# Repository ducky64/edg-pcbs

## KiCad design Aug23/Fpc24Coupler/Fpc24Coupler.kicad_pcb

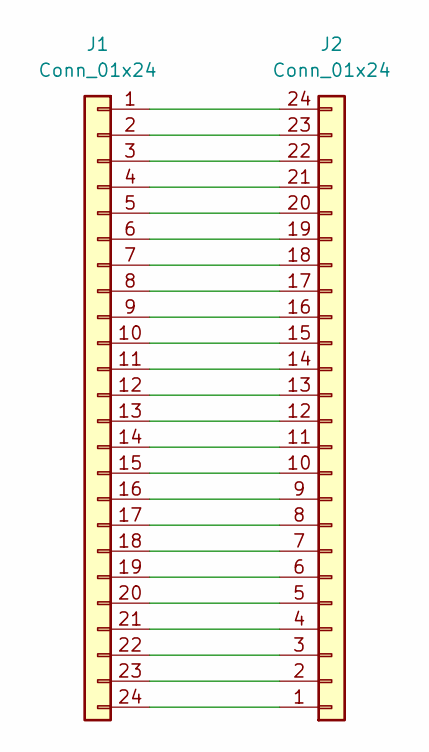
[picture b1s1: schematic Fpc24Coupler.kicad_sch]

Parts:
J1, J2: Conn_01x24; Hirose_FH12-24S-0.5SH_1x24-1MP_P0.50mm_Horizontal

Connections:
unnamed: J1.1, J2.24
unnamed: J1.2, J2.23
unnamed: J1.3, J2.22
unnamed: J1.4, J2.21
unnamed: J1.5, J2.20
unnamed: J1.6, J2.19
unnamed: J1.7, J2.18
unnamed: J1.8, J2.17
unnamed: J1.9, J2.16
unnamed: J1.10, J2.15
unnamed: J1.11, J2.14
unnamed: J1.12, J2.13
unnamed: J1.13, J2.12
unnamed: J1.14, J2.11
unnamed: J1.15, J2.10
unnamed: J1.16, J2.9
unnamed: J1.17, J2.8
unnamed: J1.18, J2.7
unnamed: J1.19, J2.6
unnamed: J1.20, J2.5
unnamed: J1.21, J2.4
unnamed: J1.22, J2.3
unnamed: J1.23, J2.2
unnamed: J1.24, J2.1

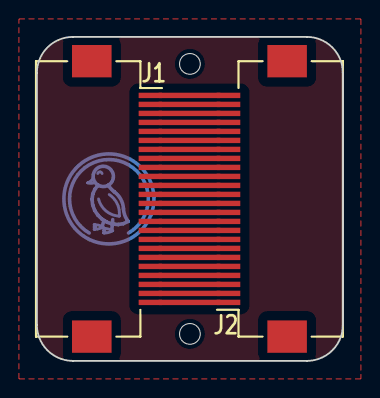
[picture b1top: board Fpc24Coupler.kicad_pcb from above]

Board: 2 copper layers, 17.0 x 18.0 mm, 4 parts (2 on the bottom side), 24 nets.

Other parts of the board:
UU4: Duck; Symbol_Duckling
UU5: Lemur; Symbol_LemurSmall

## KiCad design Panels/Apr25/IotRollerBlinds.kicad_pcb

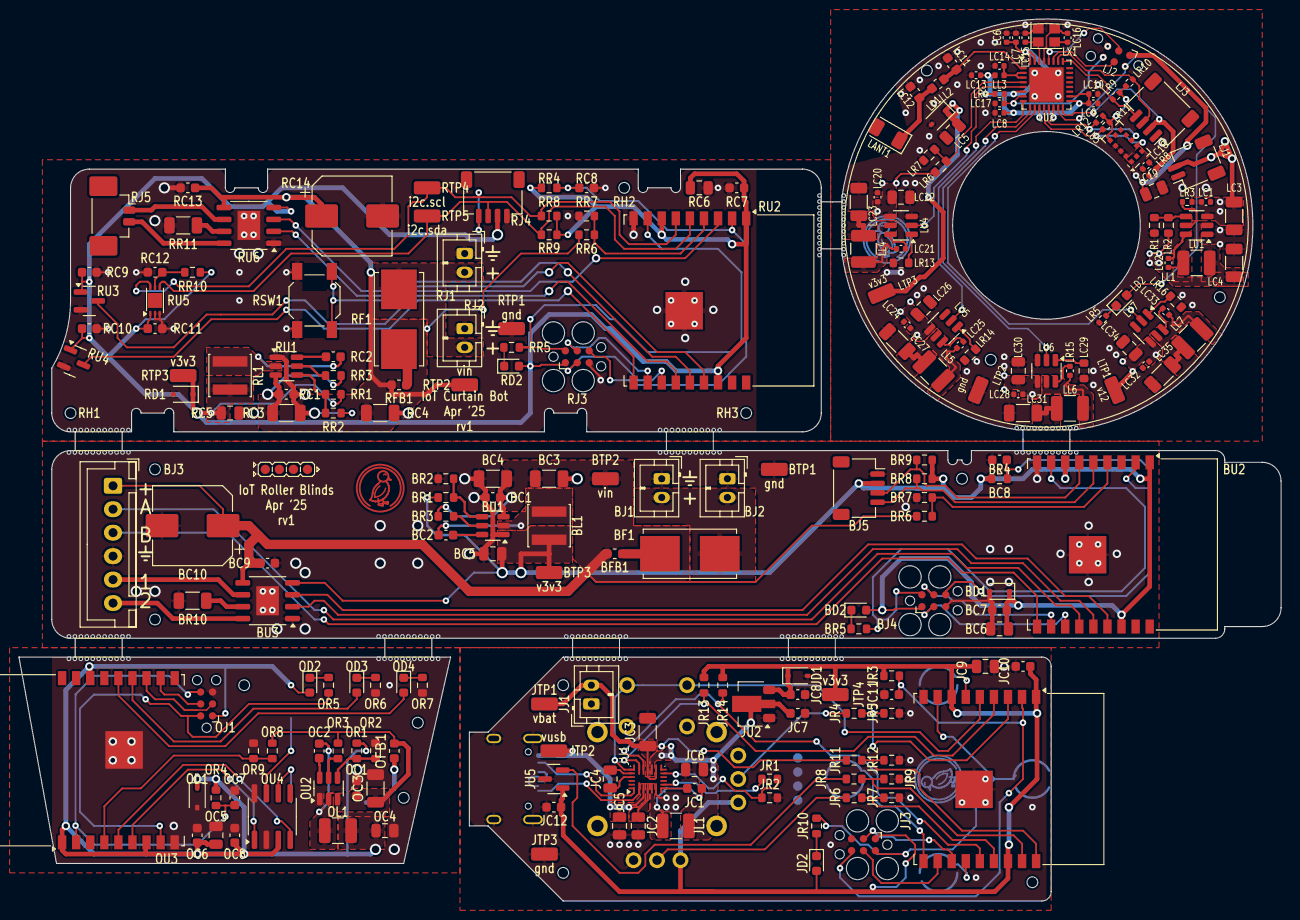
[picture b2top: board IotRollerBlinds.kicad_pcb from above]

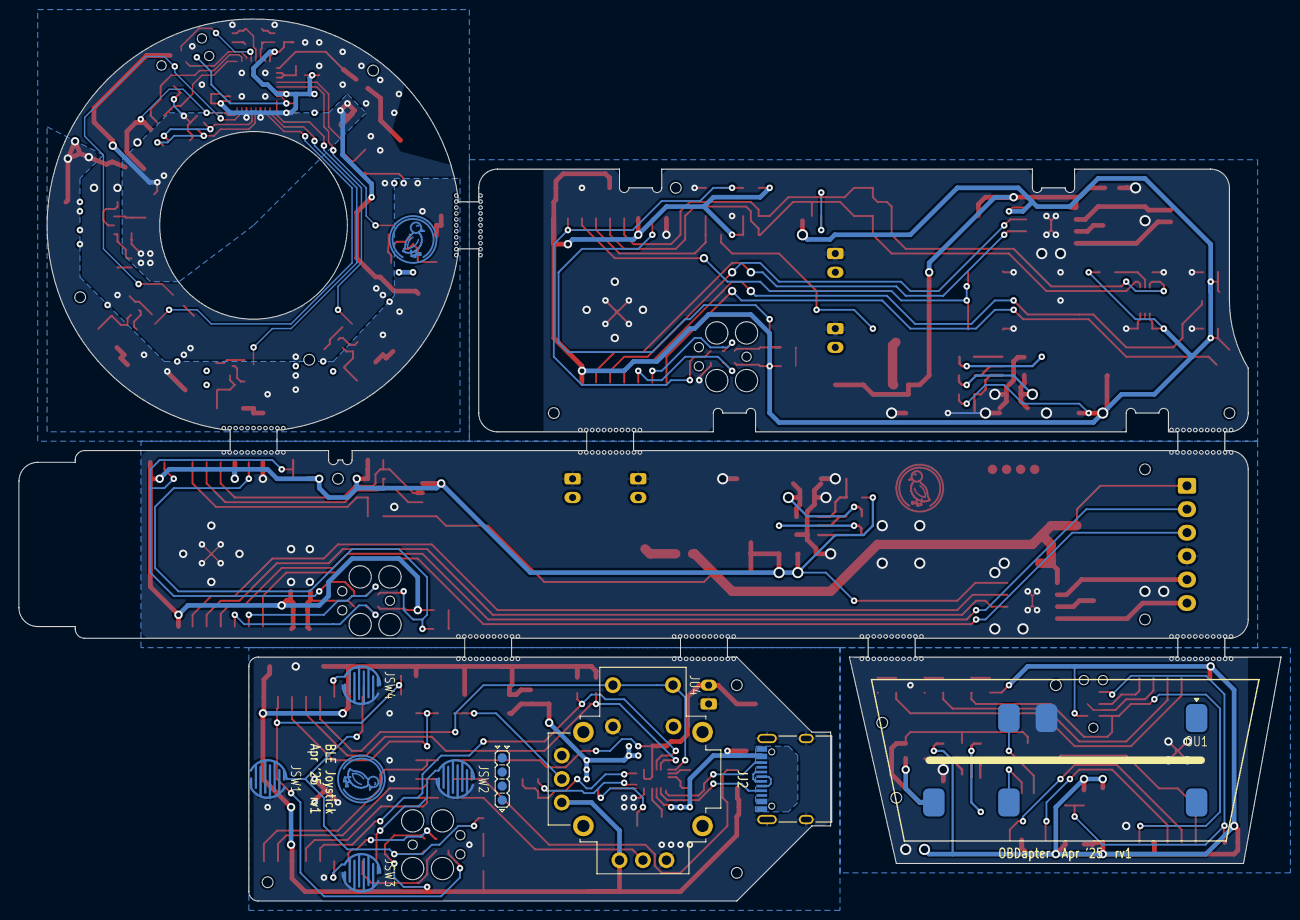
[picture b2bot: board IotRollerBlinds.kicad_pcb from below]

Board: 2 copper layers, 134.5 x 94.0 mm, 249 parts (9 on the bottom side), 148 nets.

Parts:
BC1: reg_3v3.hf_in_cap; C_0603_1608Metric
BC2: reg_3v3.boot_cap; C_0603_1608Metric
BC3: reg_3v3.power_path.in_cap.c[0]; C_1206_3216Metric
BC4: reg_3v3.power_path.in_cap.c[1]; C_1206_3216Metric
BC5: reg_3v3.power_path.out_cap; C_0805_2012Metric
BC6: mcu.vcc_cap0; C_0805_2012Metric
BC7: mcu.vcc_cap1; C_0603_1608Metric
BC8: mcu.en_pull.c; C_0603_1608Metric
BC9: drv.vm_cap0; C_0603_1608Metric
BC10: drv.vm_cap1; CP_Elec_8x10
BD1: prot_3v3; D_SOD-323
BD2: ledr.package; LED_0603_1608Metric
BF1: fuse; Fuseholder_Littelfuse_Nano2_154x
BFB1: ferrite; L_0603_1608Metric
BH1: jlc_th.th1; JlcToolingHole_1.152mm
BH2: jlc_th.th2; JlcToolingHole_1.152mm
BH3: jlc_th.th3; JlcToolingHole_1.152mm
BJ1: pwr; JST_PH_B2B-PH-K_1x02_P2.00mm_Vertical
BJ2: pwr_out; JST_PH_B2B-PH-K_1x02_P2.00mm_Vertical
BJ3: conn; JST_XH_B6B-XH-A_1x06_P2.50mm_Vertical
BJ4: mcu.prog; Tag-Connect_TC2030-IDC-FP_2x03_P1.27mm_Vertical
BJ5: qwiic; JST_SH_SM04B-SRSS-TB_1x04-1MP_P1.00mm_Horizontal
BL1: reg_3v3.power_path.inductor; L_Sunlord_SWPA4030S
BR1: reg_3v3.fb.top_res; R_0603_1608Metric
BR2: reg_3v3.fb.bottom_res; R_0603_1608Metric
BR3: reg_3v3.en_res; R_0603_1608Metric
BR4: mcu.en_pull.r; R_0603_1608Metric
BR5: ledr.res; R_0603_1608Metric
BR6: vin_sense.top_res; R_0603_1608Metric
BR7: vin_sense.bottom_res; R_0603_1608Metric
BR8: qwiic_pull.scl_res; R_0603_1608Metric
BR9: qwiic_pull.sda_res; R_0603_1608Metric
BR10: drv.isen_res; R_1206_3216Metric
BTP1: gnd; TestPoint_TE_RCT_0805
BTP2: vin; TestPoint_TE_RCT_0805
BTP3: v3v3; TestPoint_TE_RCT_0805
BU1: reg_3v3.ic; SOT-23-6
BU2: mcu.ic; ESP-WROOM-02
BU3: drv.ic; HSOP-8-1EP_3.9x4.9mm_P1.27mm_EP2.41x3.1mm
JC1: mp2722.vbst_cap; C_0603_1608Metric
JC2: mp2722.pmid_cap; C_0805_2012Metric
JC3: mp2722.batt_cap; C_1206_3216Metric
JC4: mp2722.vcc_cap; C_0805_2012Metric
JC5: mp2722.power_path.in_cap; C_0805_2012Metric
JC6: mp2722.power_path.out_cap; C_0805_2012Metric
JC7: reg_3v3.in_cap; C_0603_1608Metric
JC8: reg_3v3.out_cap; C_0603_1608Metric
JC9: mcu.vcc_cap0; C_0805_2012Metric
JC10: mcu.vcc_cap1; C_0603_1608Metric
JC11: mcu.en_pull.c; C_0603_1608Metric
JC12: trig.cbyp; C_0603_1608Metric
JD1: prot_3v3; D_SOD-323
JD2: ledr.package; LED_0603_1608Metric
JH1: jlc_th.th1; JlcToolingHole_1.152mm
JH2: jlc_th.th2; JlcToolingHole_1.152mm
JH3: jlc_th.th3; JlcToolingHole_1.152mm
JJ1: bat; JST_PH_B2B-PH-K_1x02_P2.00mm_Vertical
JJ2: usb; USB_C_Receptacle_XKB_U262-16XN-4BVC11
JJ3: mcu.prog; Tag-Connect_TC2030-IDC-FP_2x03_P1.27mm_Vertical
JL1: mp2722.power_path.inductor; L_1210_3225Metric
JR1: fake_ntc.top_res; R_0603_1608Metric
JR2: fake_ntc.bottom_res; R_0603_1608Metric
JR3: mcu.en_pull.r; R_0603_1608Metric
JR4: ax1_div.top_res; R_0603_1608Metric
JR5: ax1_div.bottom_res; R_0603_1608Metric
JR6: ax2_div.top_res; R_0603_1608Metric
JR7: ax2_div.bottom_res; R_0603_1608Metric
JR8: trig_div.top_res; R_0603_1608Metric
JR9: trig_div.bottom_res; R_0603_1608Metric
JR10: ledr.res; R_0603_1608Metric
JR11: vbat_sense.top_res; R_0603_1608Metric
JR12: vbat_sense.bottom_res; R_0603_1608Metric
JR13: i2c_pull.scl_res; R_0603_1608Metric
JR14: i2c_pull.sda_res; R_0603_1608Metric
JSW1: mcu.boot; MembraneSwitch_4mm
JSW2: sw[0]; MembraneSwitch_4mm
JSW3: sw[1]; MembraneSwitch_4mm
JSW4: sw[2]; MembraneSwitch_4mm
JTP1: vbat; TestPoint_TE_RCT_0805
JTP2: vusb; TestPoint_TE_RCT_0805
JTP3: gnd; TestPoint_TE_RCT_0805
JTP4: v3v3; TestPoint_TE_RCT_0805
JU1: mp2722.ic; MPS_QFN-22_2.5x3.5mm_P0.4mm
JU2: reg_3v3.ic; SOT-89-3
JU3: mcu.ic; ESP-WROOM-02
JU4: stick; Joystick_XboxElite2
JU5: trig.ic; SOT-23
LANT1: mcu.ant; D_1206_3216Metric
LC1: reg_3v3.hf_in_cap; C_0402_1005Metric
LC2: reg_3v3.boot_cap; C_0402_1005Metric
LC3: reg_3v3.power_path.in_cap; C_1206_3216Metric
LC4: reg_3v3.power_path.out_cap; C_1206_3216Metric
LC5: mcu.vdd_bulk_cap; C_0805_2012Metric
LC6: mcu.vdda_cap0; C_0402_1005Metric
LC7: mcu.vdda_cap1; C_0402_1005Metric
LC8: mcu.vddrtc_cap; C_0402_1005Metric
LC9: mcu.vddcpu_cap; C_0402_1005Metric
LC10: mcu.vddspi_cap; C_0402_1005Metric
LC11: mcu.pi.c1; C_0603_1608Metric
LC12: mcu.pi.c2; C_0603_1608Metric
LC13: mcu.vdd3p3_l_cap; C_0402_1005Metric
LC14: mcu.vdd3p3_cap; C_0402_1005Metric
LC15: mcu.crystal.cap_a; C_0402_1005Metric
LC16: mcu.crystal.cap_b; C_0402_1005Metric
LC17: mcu.en_pull.c; C_0402_1005Metric
LC18: tof.vdd_cap[0]; C_0402_1005Metric
LC19: tof.vdd_cap[1]; C_0805_2012Metric
LC20: led_drv[0].cap; C_0402_1005Metric
LC21: led_drv[0].boot_cap; C_0402_1005Metric
LC22: led_drv[0].power_path.in_cap; C_0805_2012Metric
LC23: led_drv[0].power_path.out_cap; C_1206_3216Metric
LC24: led_drv[1].cap; C_0402_1005Metric
LC25: led_drv[1].boot_cap; C_0402_1005Metric
LC26: led_drv[1].power_path.in_cap; C_0805_2012Metric
LC27: led_drv[1].power_path.out_cap; C_1206_3216Metric
LC28: led_drv[2].cap; C_0402_1005Metric
LC29: led_drv[2].boot_cap; C_0402_1005Metric
LC30: led_drv[2].power_path.in_cap; C_0805_2012Metric
LC31: led_drv[2].power_path.out_cap; C_1206_3216Metric
LC32: led_drv[3].cap; C_0402_1005Metric
LC33: led_drv[3].boot_cap; C_0402_1005Metric
LC34: led_drv[3].power_path.in_cap; C_0805_2012Metric
LC35: led_drv[3].power_path.out_cap; C_1206_3216Metric
LD1: prot_3v3; D_SOD-323
LD2: ledr.package; LED_0603_1608Metric
LH1: jlc_th.th1; JlcToolingHole_1.152mm
LH2: jlc_th.th2; JlcToolingHole_1.152mm
LH3: jlc_th.th3; JlcToolingHole_1.152mm
LJ1: pwr; JST_SH_SM02B-SRSS-TB_1x02-1MP_P1.00mm_Horizontal
LJ2: mcu.prog; Tag-Connect_TC2030-IDC-NL_2x03_P1.27mm_Vertical
LJ3: qwiic; JST_SH_SM04B-SRSS-TB_1x04-1MP_P1.00mm_Horizontal
LL1: reg_3v3.power_path.inductor; L_1210_3225Metric
LL2: mcu.pi.l; L_0603_1608Metric
LL3: mcu.vdd3p3_l; L_0402_1005Metric
LL4: led_drv[0].power_path.inductor; L_1210_3225Metric
LL5: led_drv[1].power_path.inductor; L_1210_3225Metric
LL6: led_drv[2].power_path.inductor; L_1210_3225Metric
LL7: led_drv[3].power_path.inductor; L_1210_3225Metric
LR1: reg_3v3.fb.top_res; R_0603_1608Metric
LR2: reg_3v3.fb.bottom_res; R_0603_1608Metric
LR3: reg_3v3.en_res; R_0402_1005Metric
LR4: mcu.en_pull.r; R_0402_1005Metric
LR5: ledr.res; R_0402_1005Metric
LR6: v12_sense.top_res; R_0603_1608Metric
LR7: v12_sense.bottom_res; R_0603_1608Metric
LR8: qwiic_pwr_res; R_0402_1005Metric
LR9: qwiic_pull.scl_res; R_0402_1005Metric
LR10: qwiic_pull.sda_res; R_0402_1005Metric
LR11: tof_pull.scl_res; R_0402_1005Metric
LR12: tof_pull.sda_res; R_0402_1005Metric
LR13: led_drv[0].rsense; R_0603_1608Metric
LR14: led_drv[1].rsense; R_0603_1608Metric
LR15: led_drv[2].rsense; R_0603_1608Metric
LR16: led_drv[3].rsense; R_0603_1608Metric
LTP1: v12; TestPoint_TE_RCT_0805
LTP2: gnd; TestPoint_TE_RCT_0805
LTP3: v3v3; TestPoint_TE_RCT_0805
LU1: reg_3v3.ic; SOT-23-6
LU2: mcu.ic; QFN-32-1EP_5x5mm_P0.5mm_EP3.65x3.65mm
LU3: tof.ic; ST_VL53L0X
LU4: led_drv[0].ic; SOT-23-6
LU5: led_drv[1].ic; SOT-23-6
LU6: led_drv[2].ic; SOT-23-6
LU7: led_drv[3].ic; SOT-23-6
LX1: mcu.crystal.package; Crystal_SMD_2520-4Pin_2.5x2.0mm
OC1: reg_3v3.hf_in_cap; C_0603_1608Metric
OC2: reg_3v3.boot_cap; C_0603_1608Metric
OC3: reg_3v3.power_path.in_cap; C_1206_3216Metric
OC4: reg_3v3.power_path.out_cap; C_0805_2012Metric
OC5: mcu.vcc_cap0; C_0805_2012Metric
OC6: mcu.vcc_cap1; C_0603_1608Metric
OC7: mcu.en_pull.c; C_0603_1608Metric
OC8: can.vdd_cap; C_0603_1608Metric
OD1: prot_3v3; D_SOD-323
OD2: ledr.package; LED_0603_1608Metric
OD3: ledg.package; LED_0603_1608Metric
OD4: ledw.package; LED_0603_1608Metric
OFB1: ferrite; L_0603_1608Metric
OH1: jlc_th.th1; JlcToolingHole_1.152mm
OH2: jlc_th.th2; JlcToolingHole_1.152mm
OH3: jlc_th.th3; JlcToolingHole_1.152mm
OJ1: mcu.prog; Tag-Connect_TC2030-IDC-NL_2x03_P1.27mm_Vertical
OL1: reg_3v3.power_path.inductor; L_1210_3225Metric
OR1: reg_3v3.fb.top_res; R_0603_1608Metric
OR2: reg_3v3.fb.bottom_res; R_0603_1608Metric
OR3: reg_3v3.en_res; R_0603_1608Metric
OR4: mcu.en_pull.r; R_0603_1608Metric
OR5: ledr.res; R_0603_1608Metric
OR6: ledg.res; R_0603_1608Metric
OR7: ledw.res; R_0603_1608Metric
OR8: vobd_sense.top_res; R_0603_1608Metric
OR9: vobd_sense.bottom_res; R_0603_1608Metric
OU1: obd; J1962
OU2: reg_3v3.ic; SOT-23-6
OU3: mcu.ic; ESP-WROOM-02
OU4: can.ic; SOIC-8_3.9x4.9mm_P1.27mm
RC1: reg_3v3.hf_in_cap; C_0603_1608Metric
RC2: reg_3v3.boot_cap; C_0603_1608Metric
RC3: reg_3v3.power_path.in_cap.c[0]; C_1206_3216Metric
RC4: reg_3v3.power_path.in_cap.c[1]; C_1206_3216Metric
RC5: reg_3v3.power_path.out_cap; C_0805_2012Metric
RC6: mcu.vcc_cap0; C_0805_2012Metric
RC7: mcu.vcc_cap1; C_0603_1608Metric
RC8: mcu.en_pull.c; C_0603_1608Metric
RC9: enca.cin; C_0603_1608Metric
RC10: encb.cin; C_0603_1608Metric
RC11: als.vcc_cap; C_0603_1608Metric
RC12: als.dvi_cap; C_0603_1608Metric
RC13: drv.vm_cap0; C_0603_1608Metric
RC14: drv.vm_cap1; CP_Elec_8x10
RD1: prot_3v3; D_SOD-323
RD2: ledr.package; LED_0603_1608Metric
RF1: fuse; Fuseholder_Littelfuse_Nano2_154x
RFB1: ferrite; L_0603_1608Metric
RH1: jlc_th.th1; JlcToolingHole_1.152mm
RH2: jlc_th.th2; JlcToolingHole_1.152mm
RH3: jlc_th.th3; JlcToolingHole_1.152mm
RJ1: pwr; JST_PH_B2B-PH-K_1x02_P2.00mm_Vertical
RJ2: pwr_out; JST_PH_B2B-PH-K_1x02_P2.00mm_Vertical
RJ3: mcu.prog; Tag-Connect_TC2030-IDC-FP_2x03_P1.27mm_Vertical
RJ4: qwiic; JST_SH_SM04B-SRSS-TB_1x04-1MP_P1.00mm_Horizontal
RJ5: motor; Molex_PicoBlade_53398-0271_1x02-1MP_P1.25mm_Vertical
RL1: reg_3v3.power_path.inductor; L_Sunlord_SWPA4030S
RR1: reg_3v3.fb.top_res; R_0603_1608Metric
RR2: reg_3v3.fb.bottom_res; R_0603_1608Metric
RR3: reg_3v3.en_res; R_0603_1608Metric
RR4: mcu.en_pull.r; R_0603_1608Metric
RR5: ledr.res; R_0603_1608Metric
RR6: vin_sense.top_res; R_0603_1608Metric
RR7: vin_sense.bottom_res; R_0603_1608Metric
RR8: i2c_pull.scl_res; R_0603_1608Metric
RR9: i2c_pull.sda_res; R_0603_1608Metric
RR10: als.dvi_res; R_0603_1608Metric
RR11: drv.isen_res; R_1206_3216Metric
RSW1: sw; SW_SPST_SKQG_WithoutStem
RTP1: gnd; TestPoint_TE_RCT_0805
RTP2: vin; TestPoint_TE_RCT_0805
RTP3: v3v3; TestPoint_TE_RCT_0805
RTP4: i2c.scl; TestPoint_TE_RCT_0805
RTP5: i2c.sda; TestPoint_TE_RCT_0805
RU1: reg_3v3.ic; SOT-23-6
RU2: mcu.ic; ESP-WROOM-02
RU3: enca.ic; SOT-23
RU4: encb.ic; SOT-23
RU5: als.ic; HVSOF6
RU6: drv.ic; HSOP-8-1EP_3.9x4.9mm_P1.27mm_EP2.41x3.1mm
UU4: Duck; Symbol_Duckling
duck: G***; Symbol_Duckling
duck#2: G***; Symbol_Duckling

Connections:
Bconn.enca: BJ3.2, BU2.13
Bconn.encb: BJ3.3, BU2.10
Bdrv.ic.isen: BR10.2, BU3.7
Bdrv.in1: BU2.15, BU3.3
Bdrv.in2: BU2.14, BU3.2
Bdrv.out1: BJ3.5, BU3.6
Bdrv.out2: BJ3.6, BU3.8
Bfuse.pwr_out: BF1.2, BFB1.1
Bgnd: BC1.2, BC3.2, BC4.2, BC5.2, BC6.2, BC7.2, BC8.2, BC9.2, BC10.2, BD1.2, BJ1.1, BJ2.1, BJ3.4, BJ4.5, BJ5.1, BR2.2, BR7.2, BR10.1, BTP1.1, BU1.1, BU2.9, BU2.19, BU3.1, BU3.9
Bledr.res.a: BD2.1, BR5.1
Bmcu.program_boot_node: BJ4.2, BR5.2, BU2.8
Bmcu.program_en_node: BC8.1, BJ4.6, BR4.2, BU2.2
Bmcu.program_uart_node.a_tx: BJ4.3, BU2.12
Bmcu.program_uart_node.b_tx: BJ4.4, BU2.11
Bqwiic_pull.i2c.scl: BJ5.4, BR8.2, BU2.5
Bqwiic_pull.i2c.sda: BJ5.3, BR9.2, BU2.6
Breg_3v3.boot_cap.neg: BC2.2, BL1.1, BU1.2
Breg_3v3.boot_cap.pos: BC2.1, BU1.6
Breg_3v3.en_res.b: BR3.2, BU1.5
Breg_3v3.fb.output: BR1.2, BR2.1, BU1.4
Bv3v3: BC5.1, BC6.1, BC7.1, BD1.1, BD2.2, BJ4.1, BJ5.2, BL1.2, BR1.1, BR4.1, BR8.1, BR9.1, BTP3.1, BU2.1, BU2.7, BU2.16, BU3.4
Bvin: BC1.1, BC3.1, BC4.1, BC9.1, BC10.1, BFB1.2, BJ3.1, BR3.1, BR6.1, BTP2.1, BU1.3, BU3.5
Bvin_raw: BF1.1, BJ1.2, BJ2.2
Bvin_sense.output: BR6.2, BR7.1, BU2.4
Jax1_div.output: JR4.2, JR5.1, JU3.3
Jax2_div.output: JR6.2, JR7.1, JU3.15
Jfake_ntc.output: JR1.2, JR2.1, JU1.10
Jgnd: JC2.2, JC3.2, JC4.2, JC5.2, JC6.2, JC7.2, JC8.2, JC9.2, JC10.2, JC11.2, JC12.2, JD1.2, JJ1.1, JJ2.A1, JJ2.A12, JJ2.B1, JJ2.B12, JJ2.S1, JJ3.5, JR2.2, JR5.2, JR7.2, JR9.2, JR12.2, JSW1.2, JSW2.2, JSW3.2, JSW4.2, JTP3.1, JU1.5, JU1.18, JU2.1, JU3.9, JU3.19, JU4.2, JU4.3, JU4.8, JU5.3
Ji2c_pull.i2c.scl: JR13.2, JU1.16, JU3.4
Ji2c_pull.i2c.sda: JR14.2, JU1.15, JU3.14
Jledr.res.a: JD2.1, JR10.1
Jmcu.program_boot_node: JJ3.2, JR10.2, JSW1.1, JU3.8
Jmcu.program_en_node: JC11.1, JJ3.6, JR3.2, JU3.2
Jmcu.program_uart_node.a_tx: JJ3.3, JU3.12
Jmcu.program_uart_node.b_tx: JJ3.4, JU3.11
Jmp2722.cc.cc1: JJ2.A5, JU1.1
Jmp2722.cc.cc2: JJ2.B5, JU1.22
Jmp2722.ic.pmid: JC2.1, JU1.3
Jmp2722.ic.vcc: JC4.1, JU1.19
Jmp2722.pwr_out: JC6.1, JC7.1, JL1.2, JU1.13, JU2.2
Jmp2722.vbst_cap.neg: JC1.2, JL1.1, JU1.4
Jmp2722.vbst_cap.pos: JC1.1, JU1.6
Jmp2722.vrntc: JR1.1, JU1.7
Jstick.ax1: JR4.1, JU4.4
Jstick.ax2: JR6.1, JU4.7
Jstick.sw: JU1.17, JU3.5, JU4.1
Jsw[0].out: JSW2.1, JU3.10
Jsw[1].out: JSW3.1, JU3.13
Jsw[2].out: JSW4.1, JU3.6
Jtrig.out: JR8.1, JU5.2
Jtrig_div.output: JR8.2, JR9.1, JU3.17
Jusb.usb.dm: JJ2.A7, JJ2.B7
Jusb.usb.dp: JJ2.A6, JJ2.B6
Jv3v3: JC8.1, JC9.1, JC10.1, JC12.1, JD1.1, JD2.2, JJ3.1, JR3.1, JR13.1, JR14.1, JTP4.1, JU2.3, JU3.1, JU3.7, JU3.16, JU4.5, JU4.6, JU5.1
Jvbat: JC3.1, JJ1.2, JR11.1, JTP1.1, JU1.12, JU1.14
Jvbat_sense.output: JR11.2, JR12.1, JU3.18
Jvusb: JC5.1, JJ2.A4, JJ2.A9, JJ2.B4, JJ2.B9, JTP2.1, JU1.2
Lgnd: LC1.2, LC3.2, LC4.2, LC5.2, LC6.2, LC7.2, LC8.2, LC9.2, LC10.2, LC11.2, LC12.2, LC13.2, LC14.2, LC15.2, LC16.2, LC17.2, LC18.2, LC19.2, LC20.2, LC22.2, LC23.2, LC24.2, LC26.2, LC27.2, LC28.2, LC30.2, LC31.2, LC32.2, LC34.2, LC35.2, LD1.2, LJ1.1, LJ2.5, LJ3.1, LR2.2, LR5.2, LR7.2, LR13.1, LR14.1, LR15.1, LR16.1, LTP2.1, LU1.1, LU2.33, LU3.2, LU3.3, LU3.4, LU3.6, LU3.12, LU4.3, LU5.3, LU6.3, LU7.3, LX1.2, LX1.4
Lled_drv[0].boot_cap.neg: LC21.2, LL4.1, LU4.5
Lled_drv[0].boot_cap.pos: LC21.1, LU4.6
Lled_drv[0].leda: LC23.1, LL4.2
Lled_drv[0].ledk: LR13.2, LU4.1
Lled_drv[0].pwm: LU2.5, LU4.2
Lled_drv[1].boot_cap.neg: LC25.2, LL5.1, LU5.5
Lled_drv[1].boot_cap.pos: LC25.1, LU5.6
Lled_drv[1].leda: LC27.1, LL5.2
Lled_drv[1].ledk: LR14.2, LU5.1
Lled_drv[1].pwm: LU2.8, LU5.2
Lled_drv[2].boot_cap.neg: LC29.2, LL6.1, LU6.5
Lled_drv[2].boot_cap.pos: LC29.1, LU6.6
Lled_drv[2].leda: LC31.1, LL6.2
Lled_drv[2].ledk: LR15.2, LU6.1
Lled_drv[2].pwm: LU2.9, LU6.2
Lled_drv[3].boot_cap.neg: LC33.2, LL7.1, LU7.5
Lled_drv[3].boot_cap.pos: LC33.1, LU7.6
Lled_drv[3].leda: LC35.1, LL7.2
Lled_drv[3].ledk: LR16.2, LU7.1
Lled_drv[3].pwm: LU2.10, LU7.2
Lledr.res.a: LD2.1, LR5.1
Lmcu.ic.lna_in: LC11.1, LL2.1, LU2.1
Lmcu.ic.vdd3p3: LC14.1, LL3.2, LU2.2, LU2.3
Lmcu.pi.output: LANT1.1, LC12.1, LL2.2
Lmcu.program_boot_node: LD2.2, LJ2.2, LU2.15
Lmcu.program_en_node: LC17.1, LJ2.6, LR4.2, LU2.7
Lmcu.program_uart_node.a_tx: LJ2.3, LU2.28
Lmcu.program_uart_node.b_tx: LJ2.4, LU2.27
Lmcu.xtal_node.xi: LC15.1, LU2.30, LX1.1
Lmcu.xtal_node.xo: LC16.1, LU2.29, LX1.3
Lqwiic_i2c.scl: LJ3.4, LR9.2, LU2.25
Lqwiic_i2c.sda: LJ3.3, LR10.2, LU2.26
Lqwiic_pwr_res.pwr_out: LJ3.2, LR8.2, LU2.16
Lreg_3v3.boot_cap.neg: LC2.2, LL1.1, LU1.2
Lreg_3v3.boot_cap.pos: LC2.1, LU1.6
Lreg_3v3.en_res.b: LR3.2, LU1.5
Lreg_3v3.fb.output: LR1.2, LR2.1, LU1.4
Ltof_pull.i2c.scl: LR11.2, LU2.12, LU3.10
Ltof_pull.i2c.sda: LR12.2, LU2.13, LU3.9
Lv3v3: LC4.1, LC5.1, LC6.1, LC7.1, LC8.1, LC9.1, LC10.1, LC13.1, LC18.1, LC19.1, LD1.1, LJ2.1, LL1.2, LL3.1, LR1.1, LR4.1, LR8.1, LR9.1, LR10.1, LR11.1, LR12.1, LTP3.1, LU2.6, LU2.11, LU2.14, LU2.17, LU2.18, LU2.31, LU2.32, LU3.1, LU3.5, LU3.11
Lv12: LC1.1, LC3.1, LC20.1, LC22.1, LC24.1, LC26.1, LC28.1, LC30.1, LC32.1, LC34.1, LJ1.2, LR3.1, LR6.1, LTP1.1, LU1.3, LU4.4, LU5.4, LU6.4, LU7.4
Lv12_sense.output: LR6.2, LR7.1, LU2.4
Ocan.can.canh: OU1.6, OU4.7
Ocan.can.canl: OU1.14, OU4.6
Ocan.controller.rxd: OU3.5, OU4.4
Ocan.controller.txd: OU3.6, OU4.1
Ognd: OC1.2, OC3.2, OC4.2, OC5.2, OC6.2, OC7.2, OC8.2, OD1.2, OJ1.5, OR2.2, OR6.2, OR7.2, OR9.2, OU1.5, OU2.1, OU3.9, OU3.19, OU4.2, OU4.8
Oledg.res.a: OD3.1, OR6.1
Oledg.signal: OD3.2, OU3.13
Oledr.res.a: OD2.1, OR5.1
Oledw.res.a: OD4.1, OR7.1
Oledw.signal: OD4.2, OU3.14
Omcu.program_boot_node: OJ1.2, OR5.2, OU3.8
Omcu.program_en_node: OC7.1, OJ1.6, OR4.2, OU3.2
Omcu.program_uart_node.a_tx: OJ1.3, OU3.12
Omcu.program_uart_node.b_tx: OJ1.4, OU3.11
Oobd.pwr: OFB1.1, OU1.16
Oreg_3v3.boot_cap.neg: OC2.2, OL1.1, OU2.2
Oreg_3v3.boot_cap.pos: OC2.1, OU2.6
Oreg_3v3.en_res.b: OR3.2, OU2.5
Oreg_3v3.fb.output: OR1.2, OR2.1, OU2.4
Ov3v3: OC4.1, OC5.1, OC6.1, OC8.1, OD1.1, OD2.2, OJ1.1, OL1.2, OR1.1, OR4.1, OU3.1, OU3.7, OU3.16, OU4.3
Ovobd: OC1.1, OC3.1, OFB1.2, OR3.1, OR8.1, OU2.3
Ovobd_sense.output: OR8.2, OR9.1, OU3.4
Rals.dvi_res.b: RC12.1, RR10.2, RU5.5
Rdrv.ic.isen: RR11.2, RU6.7
Rdrv.in1: RU2.14, RU6.3
Rdrv.in2: RU2.15, RU6.2
Rdrv.out1: RJ5.1, RU6.6
Rdrv.out2: RJ5.2, RU6.8
Renca.out: RU2.13, RU3.3
Rencb.out: RU2.10, RU4.3
Rfuse.pwr_out: RF1.2, RFB1.1
Rgnd: RC1.2, RC3.2, RC4.2, RC5.2, RC6.2, RC7.2, RC8.2, RC9.2, RC10.2, RC11.2, RC12.2, RC13.2, RC14.2, RD1.2, RJ1.1, RJ2.1, RJ3.5, RJ4.1, RR2.2, RR7.2, RR11.1, RSW1.2, RTP1.1, RU1.1, RU2.9, RU2.19, RU3.2, RU4.2, RU5.2, RU5.3, RU6.1, RU6.9
Ri2c_chain_0.scl: RJ4.4, RR8.2, RTP4.1, RU2.6, RU5.6
Ri2c_chain_0.sda: RJ4.3, RR9.2, RTP5.1, RU2.5, RU5.4
Rledr.res.a: RD2.1, RR5.1
Rmcu.program_boot_node: RJ3.2, RR5.2, RU2.8
Rmcu.program_en_node: RC8.1, RJ3.6, RR4.2, RU2.2
Rmcu.program_uart_node.a_tx: RJ3.3, RU2.12
Rmcu.program_uart_node.b_tx: RJ3.4, RU2.11
Rreg_3v3.boot_cap.neg: RC2.2, RL1.1, RU1.2
Rreg_3v3.boot_cap.pos: RC2.1, RU1.6
Rreg_3v3.en_res.b: RR3.2, RU1.5
Rreg_3v3.fb.output: RR1.2, RR2.1, RU1.4
Rsw.out: RSW1.1, RU2.3
Rv3v3: RC5.1, RC6.1, RC7.1, RC9.1, RC10.1, RC11.1, RD1.1, RD2.2, RJ3.1, RJ4.2, RL1.2, RR1.1, RR4.1, RR8.1, RR9.1, RR10.1, RTP3.1, RU2.1, RU2.7, RU2.16, RU3.1, RU4.1, RU5.1, RU6.4
Rvin: RC1.1, RC3.1, RC4.1, RC13.1, RC14.1, RFB1.2, RR3.1, RR6.1, RTP2.1, RU1.3, RU6.5
Rvin_raw: RF1.1, RJ1.2, RJ2.2
Rvin_sense.output: RR6.2, RR7.1, RU2.4

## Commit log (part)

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2023-08-05 cleaning
2023-08-06 minimal ESP32C6 seven-segment config
2023-08-07 auto-brightness
2023-08-16 crawlerbot
2023-08-17 coupler pcb
2023-08-18 wip?
2023-08-30 cleaniing and reorg
2023-08-30 add old BLDC code
2023-08-30 skeleton code STM32
2023-08-31 wip its not going to work
2023-08-31 idk maybe doing something
2023-08-31 attempts at things
2023-08-31 END TO END COMMS YAY
2023-08-31 analog read probably working
2023-08-31 version compatibility
2023-08-31 more complex pattern
2023-09-01 timeout code for stm32 coprocessor
2023-09-01 rp2040 still dead
2023-09-18 LED driver effects
2023-10-16 panel wip
2023-10-16 wip panelization
2023-10-18 ridiculous panel
2023-10-18 OLED kinda doing something
2023-10-18 draw point function - really slow though
2023-10-19 gerbers as sent to fab
2023-10-25 stm32l432 test skeleton broken
2023-10-25 break up big main; add PS3 controller (broken)
2023-10-25 well thats unfortunate
2023-10-25 fix fan driver io
2023-10-26 crawlerbot demo pinmaps
2023-10-28 solo1-based tsc code
2023-10-28 docs
2023-10-29 iron controller working
2023-10-30 broken USB PD wip
2023-10-30 its communicating
2023-10-30 wip def broken
2023-10-30 wip custom component
2023-10-30 PROGRESS
2023-10-31 a bit less red
2023-10-31 multisensor component
2023-10-31 work on porting the PD FSM
2023-10-31 CC detection working, kinda
2023-10-31 serious wip
2023-10-31 logging working
2023-10-31 compResult stable now
2023-10-31 read out capabilitties
2023-10-31 binary search vbus measurement
2023-10-31 vbus measurement
2023-10-31 better behavior on replug
2023-11-01 set voltages yay
2023-11-01 fix cold start bug
2023-11-01 wip mcpwm
2023-11-01 cleanup
2023-11-01 MCPWM synchronous converter
2023-11-01 plumb target voltages through
2023-11-01 read out PD selected V and I
2023-11-01 lol 420mV is pretty bad resolution
2023-11-02 watts to pwm - not enough resolution though
2023-11-02 kinda calibrated with builtin pid component
2023-11-02 well c6 still isn't fully supported =(
2023-11-03 woohoo 32C6 operating kinda
2023-11-05 higher resolution mcpwm
2023-11-05 better pwm resolution + deadtime pwm comp
2023-11-06 iron power control
2023-11-06 separate power readout
2023-11-06 read out iron resistance
2023-11-06 cleaned up local interface and calibrations
2023-11-06 tuning
2023-11-07 configure for psram
2023-11-07 logging, HTTPS GET, and NTP sync
2023-11-07 wifi powerdown
2023-11-07 broken =(
2023-11-08 logging and debugging
2023-11-10 add touch sensor, clean up the rest
2023-11-22 somewhat untested streaming controller
2023-11-22 wip nbo
2023-11-22 less weirdness lol
2024-01-04 7-color epd test
2024-01-04 local png decoding
2024-01-06 USB SMU fabdata
2024-01-15 wip epd not working
2024-01-15 wip fetch and decode kinda working
2024-01-15 more efficient
2024-01-16 wip leds meaning something
2024-01-16 ... because the new version is even more broken ...
2024-01-16 tmp1075n modification
2024-01-16 mcp3561 skeleton
2024-01-16 skeleton continued
2024-01-16 wip mux maps
2024-01-16 plumbing through configs
2024-01-16 because oleds
2024-01-17 OLED actually working
2024-01-17 wip doesn't seem to be doing much
2024-01-17 FUSB302 robustness to unavailable sensors
2024-01-17 nonfatal failure
2024-01-17 stuff is STILL broken
2024-01-17 readback works, lol it's an addressing error
2024-01-17 adc detecting
2024-01-19 a/d kinda operating
2024-01-19 convert to abs voltage
2024-01-19 bootstrap driver
2024-01-19 number UI
2024-01-19 driver enable control
2024-01-20 dac skeleton
2024-01-20 building
2024-01-21 4378 driver
2024-01-21 DAC kinda doing something as uncalibrated as it is
2024-01-21 buck converter
2024-01-21 refactor out mcpwm to its own component, add booster
2024-01-21 naming lol
2024-01-21 buck-boost, refactor / centralize globals
2024-01-21 calibration
2024-01-21 init buckboost
2024-01-21 adc conversion timeout warning
2024-01-23 no autoreboot
2024-01-23 unhackify some stuff - looks like some bugs were from maybe ESD
2024-01-23 still really brken
2024-01-23 well. it does something.
2024-01-23 3D EPD working
2024-01-23 wow the 3c is SO STABLE
2024-01-23 use the full 3c
2024-01-28 USB SMU client baby steps
2024-01-28 cleaning of mcp adc code, add raw adc counts
2024-01-28 liveness dot
2024-01-29 aioesphomeapi works on linux only without excess delays
2024-01-29 calibration script
2024-01-29 pretty good calibration data actually
2024-01-29 self cal routine + data
    wtf is going on?!
2024-01-29 caldata
2024-01-30 more caldata
2024-01-30 smu rest api wip
2024-01-30 optional plotting mode
2024-01-30 wip new cal
2024-01-30 wip calibration
2024-01-30 IV trace mode
2024-01-31 fix a config
2024-02-09 kinda local controls buttons dont make sense at all
2024-02-09 IV-plot for LED
2024-02-19 boxes
2024-03-06 eink fabdata
2024-04-22 UsbSmuV3
2024-04-25 update iot display for new eink board
2024-04-26 safer start
2024-04-26 iot display deep sleep
2024-05-01 wip not really working
2024-05-01 fix polarity
2024-05-07 timeout / error handling code
2024-05-07 end to end again
2024-05-08 red channel support
2024-05-08 better vsense code
2024-05-08 support indexed mode
2024-05-08 optional comp pin for mcpwm sync
2024-05-08 more instrumentation
2024-05-08 asynchronous conversions
2024-05-08 more meaningful display nums
2024-05-08 fix deep sleep overflow?
2024-05-08 range filter skeleton
2024-05-08 filters maybe?
2024-05-08 skeleton
2024-05-09 range filter
2024-05-11 autocal script
2024-05-11 wip preliminary cal data
2024-05-20 more current
2024-05-21 amps cal
2024-05-23 characterization
2024-05-23 ranging code
2024-05-23 fix irange
2024-05-23 integrated energy and ah
2024-05-23 cal-corrected low range sweep
2024-06-11 eink display 1.1 as shipped
2024-06-11 cal sweeps
2024-06-11 cal data
2024-06-15 separate meta / image gets
2024-06-15 less spam
2024-06-16 untested OTA code
2024-06-16 broken OTA
2024-06-16 working OTA
2024-06-16 auto rollback
2024-06-17 restore on cal factors
2024-06-18 Add power gate code
2024-06-18 report full mac address
2024-06-18 wip cal api
2024-06-18 auto voltage cal
2024-06-18 clean cal readout
2024-06-18 amps cal revamp
2024-06-18 ranging + current cal
2024-06-18 reset integrators button
2024-06-18 dashboard cleanup
2024-06-26 mvp case design
2024-06-26 lcd cleanup
2024-06-28 cal dump tool
2024-06-28 simplify cal architecture and calltool
2024-06-28 rounding + local UI
2024-06-28 simplify front panel
2024-06-29 better anticrossover
2024-06-29 sample buffer skeleton
2024-06-30 working sample buffer
2024-06-30 sample buffer dump tool
2024-06-30 full rows
2024-06-30 callback with LEDs and stuff
2024-06-30 sleep during busy
2024-06-30 use internal adc calibration
2024-06-30 variable attenuation adc
2024-07-01 calibrated adc read
2024-07-02 disconnected / invalid display time as grounds for rollback
2024-07-02 fix cal for latest esphome version?
2024-07-03 wip untested
2024-07-04 proper ranging support
2024-07-04 revamped display
2024-07-04 local select interface
2024-07-04 display cleanup
2024-07-04 integrators wip
2024-07-04 cleaned up integrator code
2024-07-04 ranging disable
2024-07-04 enable ranging config
2024-07-06 precharge
2024-07-06 prevent backpowering
2024-07-07 experimental code for 13.3" display
2024-07-07 fix voltage readout
2024-07-07 broken ACeP code
2024-07-08 update for 13.3 display
2024-09-06 more compact self-data display
2024-09-06 on-device dithering
2024-09-06 proper dithering
2024-09-16 fix PD driver
2024-09-26 add EPD busy grace, add RSSI and last display time to stats
2024-09-26 v9 extended grace
2024-10-01 release spi and display lines
2024-10-01 dimmer LEDs
2024-10-04 mostly implemented?
2024-10-04 less spamtastic
2024-10-06 move things
2024-10-06 esplora panel
2024-11-21 mechanical prototype 1
2024-11-23 overflow-save millis comparisons; screen timeout
2025-01-14 timeout LEDs
2025-06-07 Add WDT support to e-cal display (#1)
    Add a 8-second WDT to prevent firmware from getting stuck. WDT trips are treated as a failure for failure counting and reporting.
    Also reduces some stabilization delays, seems to work.
2025-07-01 wip fabdata
2025-07-01 as ordered
2025-07-21 bottom + range
2025-07-21 fault detection + tuning
2025-09-06 MP2722 bidi test
2025-09-06 7-segment: better comments, add bleproxy
2025-09-07 roller blinds mechanical
2025-10-04 esp-generate output
2025-10-04 to blinky
2025-10-04 embassy tasks
2025-11-09 SMU3.1 wip
2025-11-09 usbsmu netlist
2025-11-09 update netlist
2025-11-19 updated for production
2026-02-14 crawlerbot fw
2026-02-14 SMU3.1 fabdata (#2)
    * SMU3.1 wip
    * Delete gerbers.zip
    * usbsmu netlist
    * update netlist
    * updated for production
    * update
2026-06-23 wip mega panel
2026-06-24 production data
